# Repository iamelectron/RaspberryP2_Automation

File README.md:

# RaspberryP2_Automation 
Raspberry Pi Windows IoT Home Automation
WindowsIoT Raspberry Pi - Fully Commented Raspberry Pi's GUI app WindowsIoTAutomation - Android Studio Datagram - WIndows App - Universal Windows App (Demo) pic18_nrf.X 0 - PIC microcontroller program (Slave Device)

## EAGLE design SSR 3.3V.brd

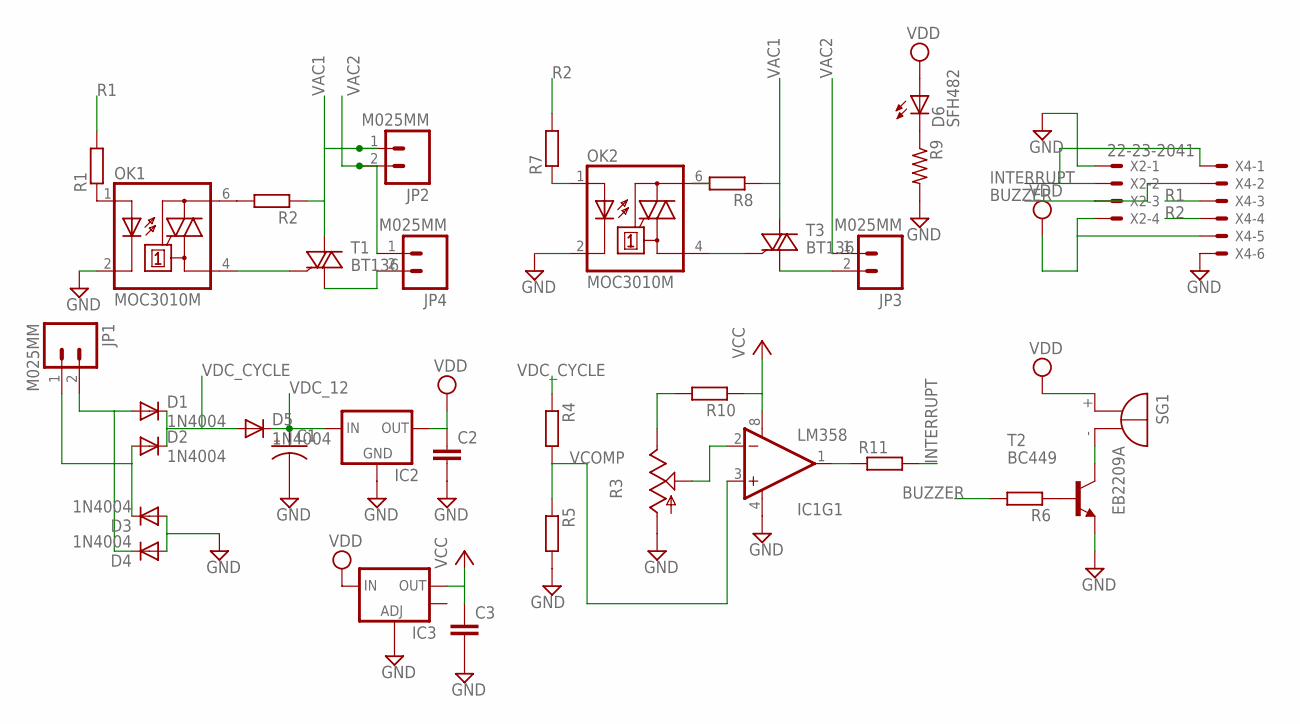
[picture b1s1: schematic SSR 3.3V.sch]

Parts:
C1: CPOL-USE3.5-10; E3,5-10
C2, C3: CC1206; C1206
D1, D2, D3, D4, D5: 1N4004; DO41-10
D6: SFH482
IC1: LM358; DIP08
IC2: V_REG_78XX-TO-220; TO-220-ALT
IC3: V_REG_LM1117SOT223; SOT223
JP1, JP2, JP3, JP4: M025MM; SCREWTERMINAL-5MM-2
OK1, OK2: MOC3010M; DIL06
R1, R2, R5, R6, R7, R8, R10: R-EU_0204/7; 0204/7
R3: TRIM_US-CA9V; CA9V
R4, R11: R-EU_0207/12; 0207/12
R9: R-US_0207/10; 0207/10
SG1: EB2209A
T1, T3: BT136; TO220AB
T2: BC449; TO92-EBC
X2: 22-23-2041
X4: 22-23-2061

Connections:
BUZZER: R6.2, X2.3, X4.2
GND: C1.-, C2.2, C3.2, D3.A, D4.A, IC1.4 (V-), IC2.GND, IC3.1 (ADJ), OK1.2 (C), OK2.2 (C), R3.A, R5.2, R9.2, T2.E, X2.1, X4.6
INTERRUPT: R11.2, X2.2, X4.1
unnamed: OK1.1 (A), R1.1
unnamed: R3.E, R10.2
unnamed: IC1.1 (OUT), R11.1
unnamed: OK1.6 (A2), R2.2
unnamed: IC1.2 (-IN), R3.S
unnamed: OK1.4 (A1), T1.3 (G)
unnamed: R6.1, T2.B
unnamed: JP4.2, T1.1 (A1)
unnamed: SG1.-, T2.C
unnamed: D6.K (C), R9.1
unnamed: OK2.1 (A), R7.1
unnamed: OK2.6 (A2), R8.2
unnamed: OK2.4 (A1), T3.3 (G)
unnamed: JP3.2, T3.1 (A1)
R1: R1.2, X4.3
R2: R7.2, X4.4
VAC: D1.A, D4.C, JP1.2
VAC1: JP2.1, R2.1, R8.1, T1.2 (A2), T3.2 (A2)
VAC2: JP2.2, JP3.1, JP4.1
VAC_: D2.A, D3.C, JP1.1
VCC: C3.1, IC1.8 (V+), IC3.2 (OUT), R10.1
VCOMP: IC1.3 (+IN), R4.2, R5.1
VDC_12: C1.+, D5.C, IC2.IN
VDC_CYCLE: D1.C, D2.C, D5.A, R4.1
VDD: C2.1, D6.A, IC2.OUT, IC3.3 (IN), SG1.+, X2.4, X4.5

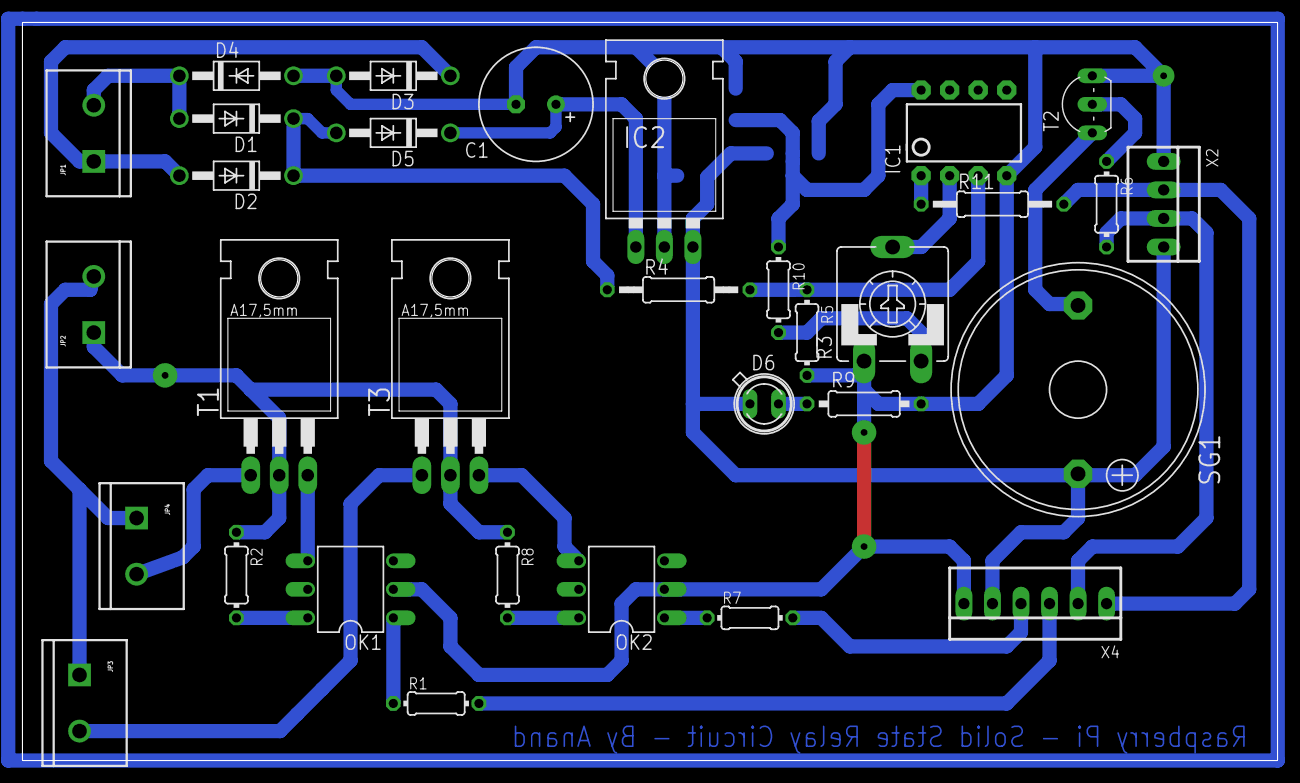
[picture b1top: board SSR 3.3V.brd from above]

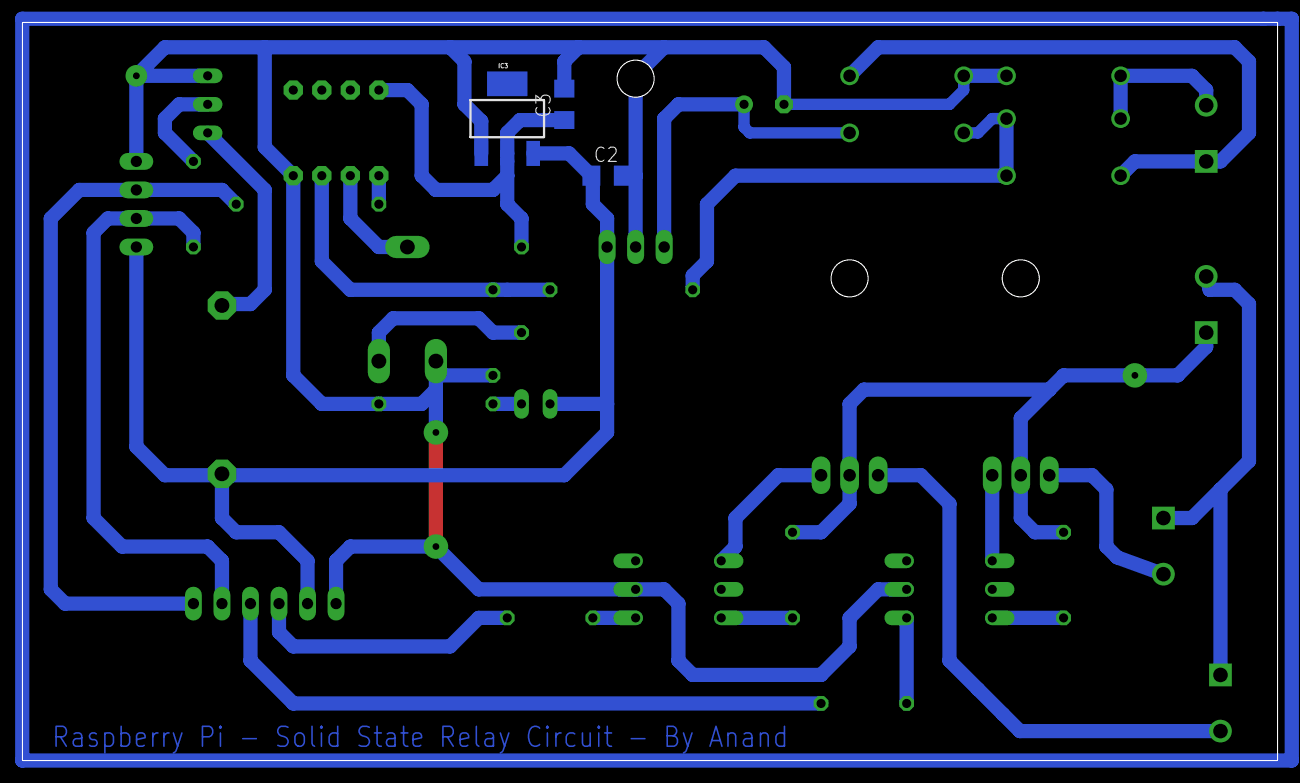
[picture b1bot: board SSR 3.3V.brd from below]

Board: 2 copper layers, 111.7 x 65.7 mm, 35 parts (3 on the bottom side), 28 nets.

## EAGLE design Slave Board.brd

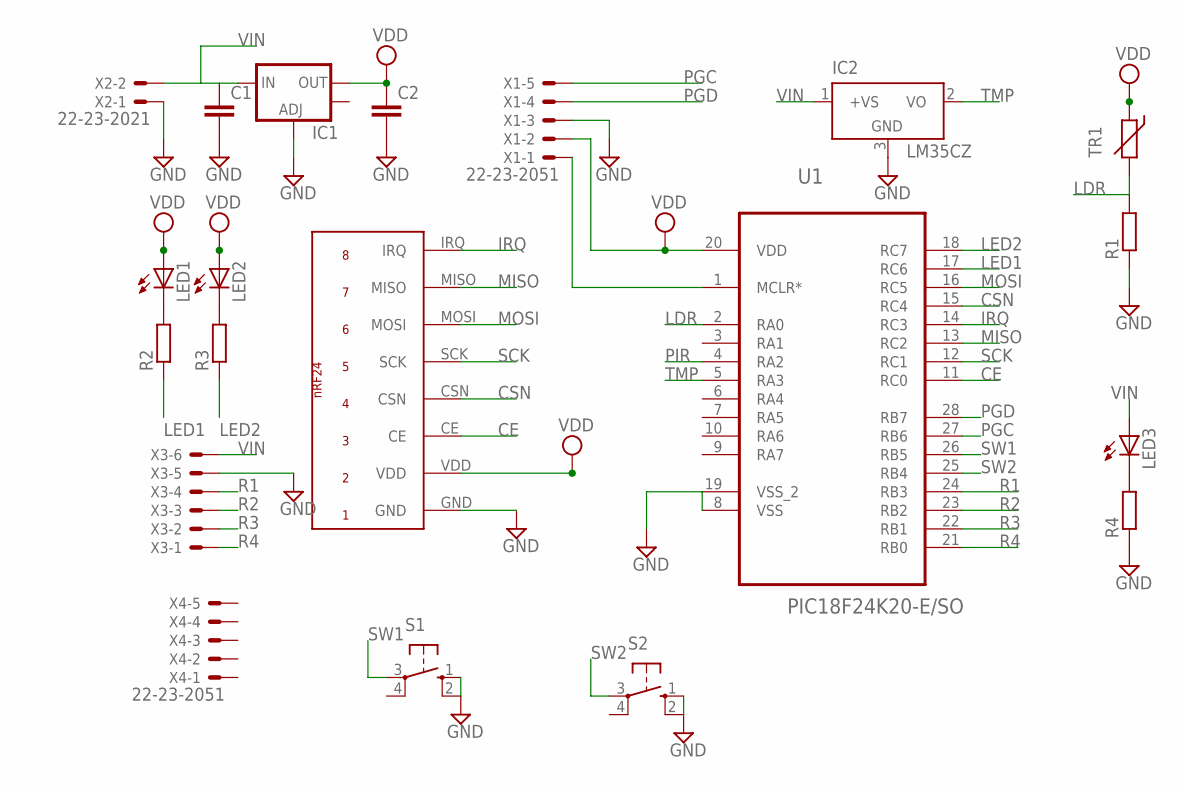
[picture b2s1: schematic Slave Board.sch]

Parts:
C1, C2: CAP1206; 1206
IC1: V_REG_LM1117SOT223; SOT223
IC2: LM35CZ; TO92
LED1, LED2, LED3: LEDKA-3528ASYC; KA-3528ASYC
R1: R-EU_0204/7; 0204/7
R2, R3: R0204/7; 0204/7
R4: RR1206; R1206
S1, S2: 10-XX; B3F-10XX
TR1: THERMISTOR_R-7,5; R-7,5
U1: PIC18F24K20-E/SO; SOIC127P1030X265-28N
U$1: NRF24
X1, X4: 22-23-2051
X2: 22-23-2021
X3: 22-23-2061

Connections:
CE: U1.11 (RC0), U$1.CE
CSN: U1.15 (RC4), U$1.CSN
GND: C1.2, C2.2, IC1.1 (ADJ), IC2.3 (GND), R1.1, R4.1, S1.1 (S), S2.1 (S), U1.8 (VSS), U1.19 (VSS_2), U$1.GND, X1.3, X2.1, X3.5
IRQ: U1.14 (RC3), U$1.IRQ
LDR: R1.2, TR1.2, U1.2 (RA0)
LED1: R2.1, U1.17 (RC6)
LED2: R3.1, U1.18 (RC7)
MISO: U1.13 (RC2), U$1.MISO
MOSI: U1.16 (RC5), U$1.MOSI
unnamed: U1.1 (MCLR*), X1.1
unnamed: LED1.C, R2.2
unnamed: LED2.C, R3.2
unnamed: LED3.C, R4.2
PGC: U1.27 (RB6), X1.5
PGD: U1.28 (RB7), X1.4
R1: U1.24 (RB3), X3.4
R2: U1.23 (RB2), X3.3
R3: U1.22 (RB1), X3.2
R4: U1.21 (RB0), X3.1
SCK: U1.12 (RC1), U$1.SCK
SW1: S1.3, U1.26 (RB5)
SW2: S2.3, U1.25 (RB4)
TMP: IC2.2 (VO), U1.5 (RA3)
VDD: C2.1, IC1.2 (OUT), LED1.A, LED2.A, TR1.1, U1.20 (VDD), U$1.VDD, X1.2
VIN: C1.1, IC1.3 (IN), IC2.1 (+VS), LED3.A, X2.2, X3.6

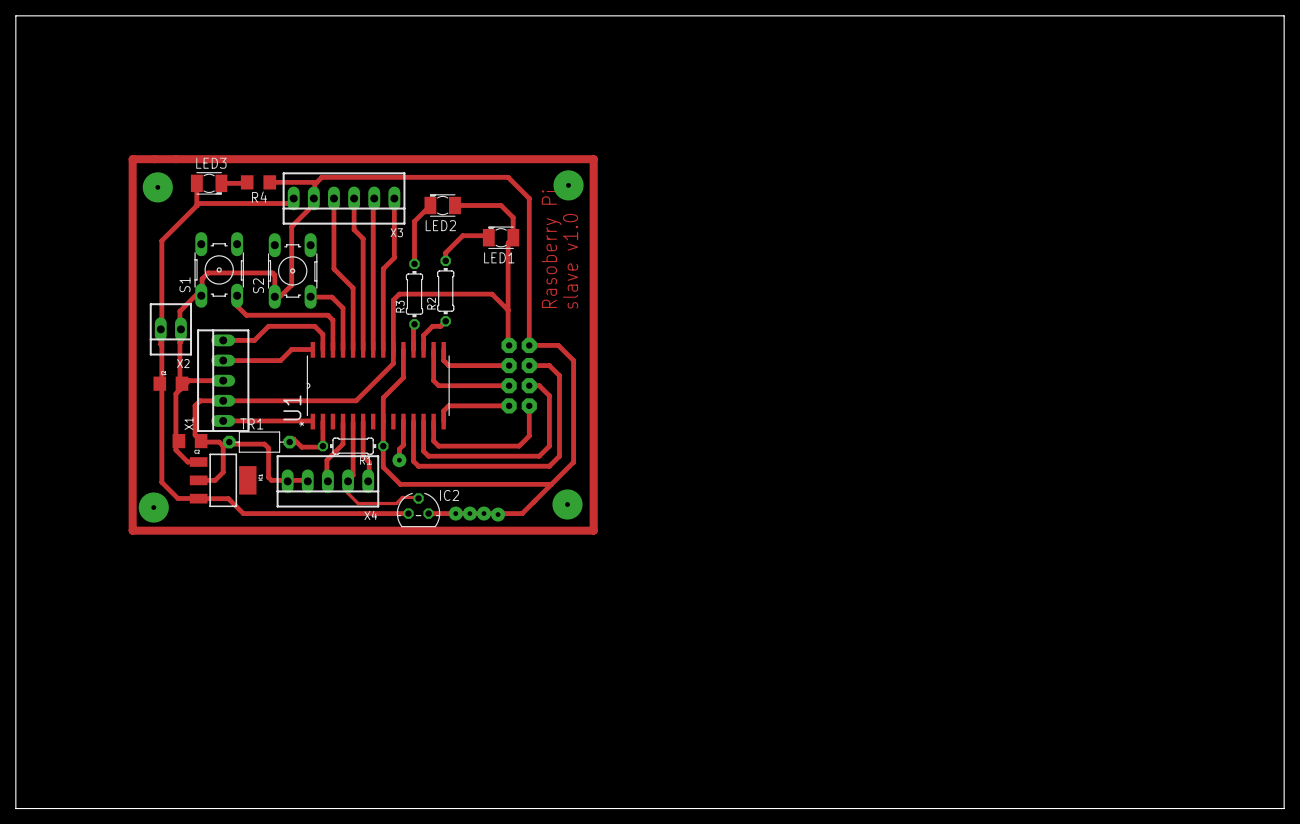
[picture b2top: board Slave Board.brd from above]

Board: 2 copper layers, 160.0 x 100.0 mm, 20 parts (1 on the bottom side), 25 nets.

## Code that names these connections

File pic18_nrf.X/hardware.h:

/* 
 * File:   hardware.h
 * Author: Anand
 *
 * Created on August 22, 2015, 1:27 PM
 */

#ifndef HARDWARE_H
#define	HARDWARE_H

#ifdef	__cplusplus
extern "C" {
#endif

     
#define _XTAL_FREQ	(16000000L)
#include <xc.h>
    
     
    ///////LED1 Direction & State
#define LED1        LATCbits.LC7
#define LED1Tris    TRISCbits.RC7
    ///////LED2 Direction & State
#define LED2        LATCbits.LC6
#define LED2Tris    TRISCbits.RC6
    
    //SW1 Direction and Read
#define SW1_Tris    TRISBbits.TRISB5
#define SW1         PORTBbits.RB5
    
    //SW1 Direction and Read    
#define SW2_Tris    TRISBbits.TRISB4
#define SW2         PORTBbits.RB4
     
///RELAY IO
#define R1_TRIS    TRISBbits.RB3
#define R2_TRIS    TRISBbits.RB2 
#define R3_TRIS    TRISBbits.RB1
#define R4_TRIS    TRISBbits.RB0    

#define R1    LATBbits.LATB3
#define R2    LATBbits.LATB2 
#define R3    LATBbits.LATB1
#define R4   LATBbits.LATB0    
#define BUZZER   LATBbits.LATB2         
    
#define ZEROCROSS  PORTBbits.RB0 
    
///spi enable bit 
//////////////////////////
#define CSN_TRIS    TRISCbits.RC4
#define CE_TRIS     TRISCbits.RC0  
 #define MOSItris    TRISCbits.RC5
#define MISOtris     TRISCbits.RC2    
 #define SCKtris    TRISCbits.RC1
      
#define CSN         LATCbits.LATC4
#define CE          LATCbits.LATC0
    
#define MOSI         LATCbits.LATC5
#define MISO         PORTCbits.RC2
#define SCK         LATCbits.LATC1 
 
////PIR Sensor TRIS
#define PIR_TRIS TRISAbits.TRISA2
#define PIR PORTAbits.RA2
 //Digital IO In
#define INIT_SW_IO    {PIR_TRIS = 1; INTCON2bits.nRBPU = 0;   WPUBbits.WPUB5 = 1; WPUBbits.WPUB4 = 1; SW1_Tris =1; SW2_Tris = 1;}  
 //Init LEDSs
#define INIT_LED_IO   {LED1Tris = 0; LED2Tris = 0;}       
 //Init SPI IO 
#define INIT_SPI_IO   {CSN_TRIS = 0; CE_TRIS = 0; MOSItris = 0; MISOtris = 1; SCKtris = 0;}      
//Init RELAY IO
#ifdef triac
    #define INIT_RELAY    {R1_TRIS = 0; R2_TRIS = 0; R3_TRIS = 0; R4_TRIS = 1; }
#endif

#ifdef relay
    #define INIT_RELAY    {R1_TRIS = 0; R2_TRIS = 0; R3_TRIS = 0; R4_TRIS = 0; }  
#endif
#define INIT_IO {INIT_SW_IO; INIT_LED_IO; INIT_SPI_IO; INIT_RELAY;}
    void CSNtoggle();       //Toggles CSN Pin
    void delay_ms(int);
#ifdef	__cplusplus
}
#endif

#endif	/* HARDWARE_H */

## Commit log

2015-09-14 Create VisualStudioFiles
2015-09-14 Windows IoT Raspberry Pi
    Raspberry Pi Windows IoT home automation project
2015-09-14 Comments added
2015-09-15 Added Auto Scan option
2015-09-15 Auto Update option
2015-09-16 Comments added
2015-09-28 pcb and schematics files added

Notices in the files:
parts and their libraries:
SparkFun-AnalogIC: Licensing: CC v3.0 Share-Alike You are welcome to use this library for commercial purposes.
